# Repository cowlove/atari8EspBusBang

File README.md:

# Atari 8-bit ESP32 BusBang

```text
@@@@@@@@@@@@@@@@@@@@@@@@@@@@@@@@@@@@@@@@@@@@@@@@@@@@@@@@@@@@@@@@@@@@@@@@@@@@@@@
@     _   _             _  ___  _     _ _        _____ ____  ____ _________   @
@    / \ | |_ __ _ _ __(_)( _ )| |__ (_) |_     | ____/ ___||  _ \___ /___ \  @
@   / _ \| __/ _` | '__| |/ _ \| '_ \| | __|    |  _| \___ \| |_) ||_ \ __) | @
@  / ___ \ || (_| | |  | | (_) | |_) | | |_     | |___ ___) |  __/___) / __/  @
@ /_/   \_\__\__,_|_|  |_|\___/|_.__/|_|\__|    |_____|____/|_|  |____/_____| @
@                ____            ____                    _ _ _ _              @
@               | __ ) _   _ ___| __ )  __ _ _ __   __ _| | | | |             @
@               |  _ \| | | / __|  _ \ / _` | '_ \ / _` | | | | |             @
@               | |_) | |_| \__ \ |_) | (_| | | | | (_| |_|_|_|_|             @
@               |____/ \__,_|___/____/ \__,_|_| |_|\__, (_|_|_|_)             @
@                                                  |___/                      @
@@@@@@@@@@@@@@@@@@@@@@@@@@@@@@@@@@@@@@@@@@@@@@@@@@@@@@@@@@@@@@@@@@@@@@@@@@@@@@@
READY
█
```

## About the Project

Atari8EspBusBang uses a naked ESP32-S3 dev board to bit-bang the Atari 8-bit memory bus through the PBI port. The ESP32 has enough speed to handle the 6502's memory requests, overriding base memory and emulating extended memory, multi-bank cartridges, and SIO devices.  It implements a true software-defined PBI device.  The outside world, modern ideas, and high-level code all have direct access to the stock Atari system and memory at 960MB/sec.  

This started as a bus monitor for troubleshooting a flaky 800XL. Once it became clear that the ESP32 could also *respond* to bus requests, the project grew into a software-defined PBI device— and an ultimate extreme performance exercise on the ESP32. The bus-protocol loop runs bare-metal on the ESP32's second core; the first core handles utility tasks such as networking, PBI device logic, and flash disk-image access.

This idea pushes the ESP32 to its absolute performance limit, and the lower level parts of the project are intricate.  I'd like to eventually implement a simple module interface for adding functionality and trying ideas in easy code steps without needing to mess with or understand the low-level internals of this project.  

## Building the Hardware

The KiCad designs, parts list, PCB ordering notes, and assembly notes are in the [hardware README](hardware/README.md).  Total cost is about $20, and requires only through-hole soldering of headers. 

## Building the Firmware

The project depends on a specific pinned and lightly patched version of ESP-IDF v6.1, llvm-mos-sdk, and a few other tools.  Using the provided docker image is probably the easiest way to arrange for this. 

```
./tools/container/setup-build-env.sh container-runtime    # Install software needed to run podman  
./tools/container/container.sh pull                       # fetch/build docker image (6Gb/5min)
./tools/container/container.sh flash_spiffs /dev/ttyACM0  # first-time init of flash storage
./tools/container/container.sh flash /dev/ttyACM0         # build firmware and flash esp32 
```

Or you can install this all directly on your system and run esp-idf tools directly.  
```
./tools/container/setup-build-env.sh          # installs patched esp-idf,etc in ~/opt/ (6Gb/5min)
. ~/opt/atari8esp-idf-v6.1/export.sh          # set env to run esp-idf tools
./tools/flash_spiffs -p /dev/ttyACM0          # first-time init of flash storage 
idf.py --ccache flash -p /dev/ttyACM0         # build firmware and flash esp32
```

For the pinned Podman build environment, see [`tools/container/container.sh`](tools/container/container.sh) and [its README](tools/container/README.md).

## Contributing

Bug reports and focused contributions are welcome.  Please report issues with the environment setup scripts. 

## License

Distributed under GPL-2.0. See [LICENSE.txt](LICENSE.txt).

## Contact

Jim Evans — [jim@vheavy.com](mailto:jim@vheavy.com)

Project repository: <https://github.com/cowlove/atari8EspBusBang>

Project webpage: <http://cowlove.com/atari8EspBusBang/>

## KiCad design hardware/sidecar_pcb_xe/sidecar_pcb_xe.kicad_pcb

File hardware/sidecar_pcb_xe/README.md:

# sidecar_pcb_xe: the Sidecar carrier with bare modules, XE (speculative)

[sidecar_pcb_xl](../sidecar_pcb_xl/) for the 130XE: the same circuit, but
J1 is the XE's **cartridge + ECI card edge** (the footprint of the
[eci2Pbi adapter](../eci2Pbi/)) instead of the PBI connector. The board
plugs straight into the XE, with no adapter.

**Status: autorouted, not reviewed.** Routed by
[`tools/autoroute.sh`](../tools/autoroute.sh): DRC shows no clearance errors
and nothing unconnected, and the schematic and board agree. Not checked by a
human yet, and its fit in the XE's cartridge opening isn't verified (the body
is as wide as the two tabs, 80.6 mm, plus the 15.4 mm J8 wing on the right,
and stands 40 mm above them, plus the antennas).

## J1: ECI ↔ PBI

Each card-edge pin carries the XL board's net for the PBI pin the eci2Pbi
adapter wires it to:

| Card edge | Net (PBI pin) | Card edge | Net (PBI pin) |
|---|---|---|---|
| 5, 4, 3, 2 | A0–A3 (3–6) | 10, 9, 8, L | D0–D3 (21–24) |
| C, D, E, F | A4–A7 (7–9, 11) | 6, 7, 11, M | D4–D7 (25–28) |
| H, J, P, N, K | A8–A12 (12–16) | R | READ (46) |
| D1, E1, F1 | A13–A15 (17, 18, 20) | S | PHI2 (31) |
| ECI 1-1 | EXTSEL (2) | ECI B1 | IRQ (35) |
| ECI 1-2 | RESET (34) | **ECI C1 (HALT)** | **READY (36)** |
| ECI 1-4 | MPD (43) | ECI 1-5 | AUDIO (49) |
| ECI 1-6 | REFRESH (40) | 13, ECI 1-7 | VCC50_1 (47) |
| B, ECI H1 | GND | | |

- **HALT:** the adapter joins ECI C1 (HALT) to PBI 36 (READY), so this board
  does too: the halt line works on the XE as on the XL boards.
- **Unused:** the PBI's EXTDEC, CAS, RAS and NCs have no ECI pin; nothing else
  on the board uses them. The cartridge pins S4, S5, RD4, RD5, CCTL and ECI
  D1XX and RESERVED are left open, as on the adapter.
- **5 V:** both card-edge 5 V pins go to `VCC50_1`, which J6 joins to the
  board rail, as on the XL board (fit J6 to run from the Atari; remove it when
  powering from J4/J5).

## Layout

The tabs run along the bottom edge: the ECI tab on the left, the cartridge
tab on the right (J1 is the adapter's footprint turned 180°; either face of
the board can be the front, see the adapter for which way it goes in). The
modules' antennas and the microSD slot point off the top edge; the
regulators U3 and U4 are on the back. A wing past the cartridge tab, on the
right, carries the optional NTSC jack J8 (below U2's antenna keep-out) and
its ladder R18-R21, as on the XL board (see its README, "J8"). Board
96.1 × 60.1 mm with the tabs.
`sidecar_pcb_xe.kicad_dru` lets J1's fingers run to the board edge.

DRC leftovers, as on the XL board: U1/U2 differ from the library (their
thermal vias widened to 0.3 mm, see the XL README), the modules' silkscreen
overhangs the top edge, two GND pads reach the pour through a single thermal spoke, and the
Atari8 footprint library isn't in the library table (J1's footprint is
embedded in the board).

## Files

| File | |
|---|---|
| `sidecar_pcb_xe.kicad_sch` | Generated by [`../tools/make_sidecar_xe_schematic.py`](../tools/make_sidecar_xe_schematic.py) from the XL schematic: don't edit by hand |
| `sidecar_pcb_xe.kicad_pcb` | Built by [`../tools/make_sidecar_xe_pcb.py`](../tools/make_sidecar_xe_pcb.py) (XL footprints, adapter's J1, XE placement), then autorouted |
| `sidecar_pcb_xe.kicad_pro`, `.kicad_dru` | Project and the card-edge DRC rule |

To rebuild after an XL change (see [../AGENTS.md](../AGENTS.md)):

```
S=$(mktemp -d)
kicad-cli sch export netlist -o $S/xl.net hardware/sidecar_pcb_xl/sidecar_pcb_xl.kicad_sch
kicad-cli sch export netlist -o $S/eci.net hardware/eci2Pbi/atari8EciToPbi.kicad_sch
python3 hardware/tools/make_sidecar_xe_schematic.py hardware/sidecar_pcb_xl/sidecar_pcb_xl.kicad_sch $S/xl.net \
    hardware/eci2Pbi/atari8EciToPbi.kicad_sch $S/eci.net hardware/sidecar_pcb_xe/sidecar_pcb_xe.kicad_sch
kicad-cli sch export netlist -o $S/xe.net hardware/sidecar_pcb_xe/sidecar_pcb_xe.kicad_sch
/usr/bin/python3 hardware/tools/make_sidecar_xe_pcb.py hardware/sidecar_pcb_xl/sidecar_pcb_xl.kicad_pcb \
    hardware/eci2Pbi/atari8EciToPbi.kicad_pcb $S/xe.net hardware/sidecar_pcb_xe/sidecar_pcb_xe.kicad_pcb
hardware/tools/autoroute.sh hardware/sidecar_pcb_xe/sidecar_pcb_xe.kicad_pcb $S/xe-routed.kicad_pcb 60
cp $S/xe-routed.kicad_pcb hardware/sidecar_pcb_xe/sidecar_pcb_xe.kicad_pcb
```

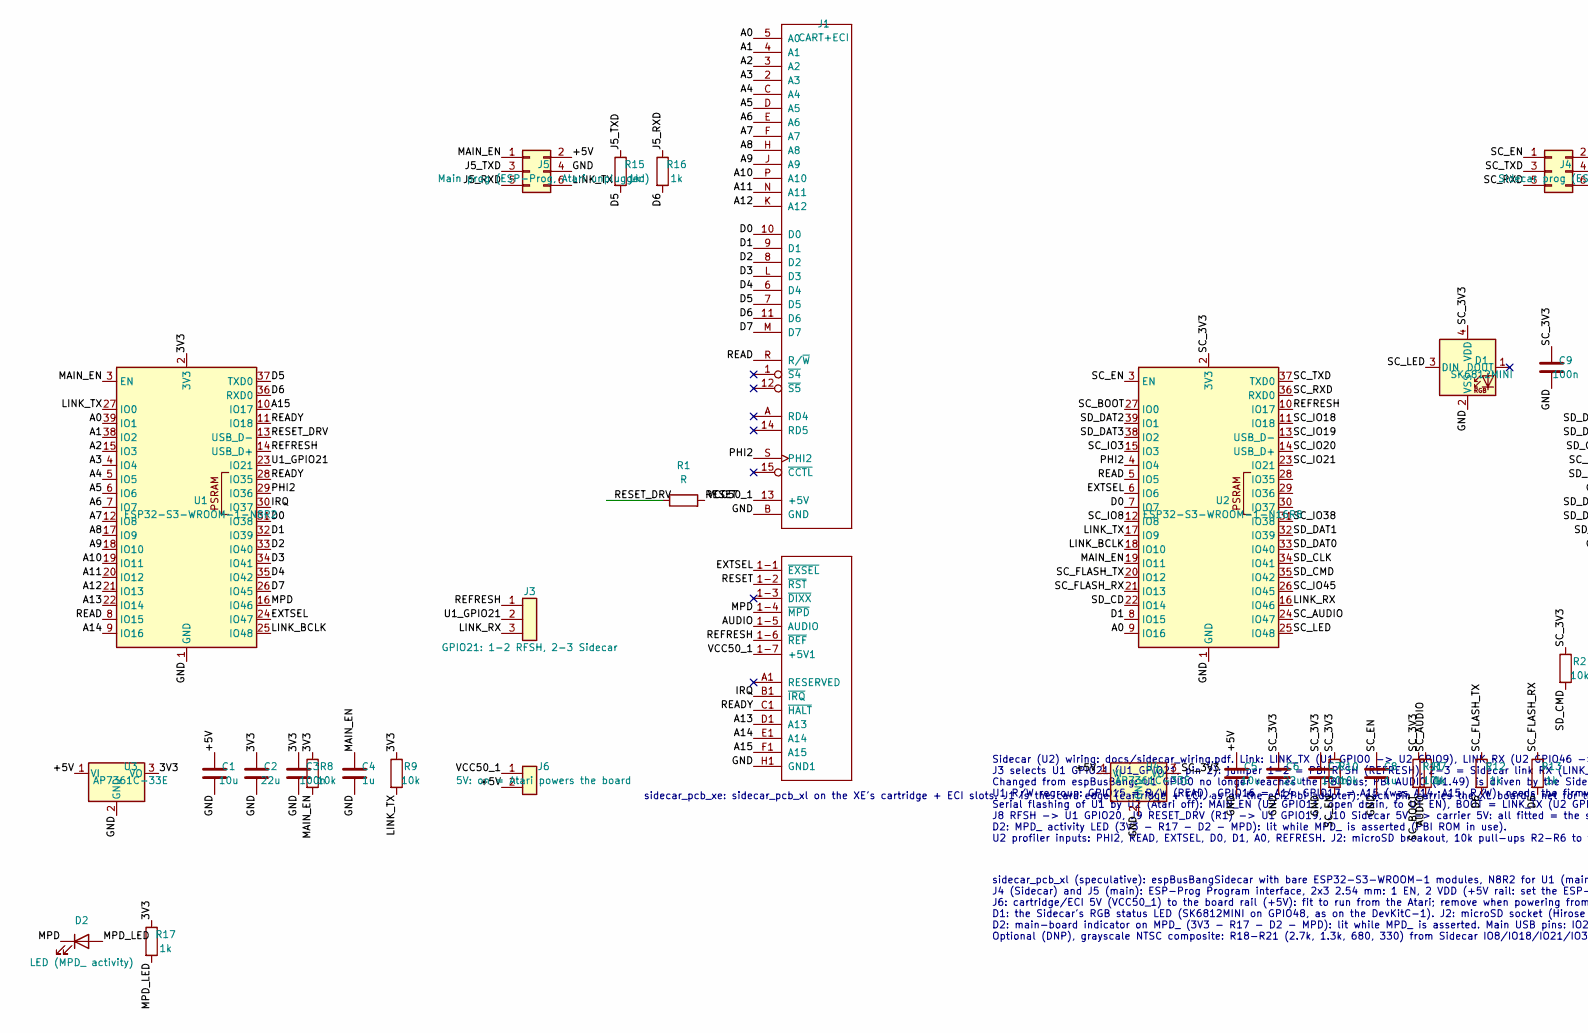
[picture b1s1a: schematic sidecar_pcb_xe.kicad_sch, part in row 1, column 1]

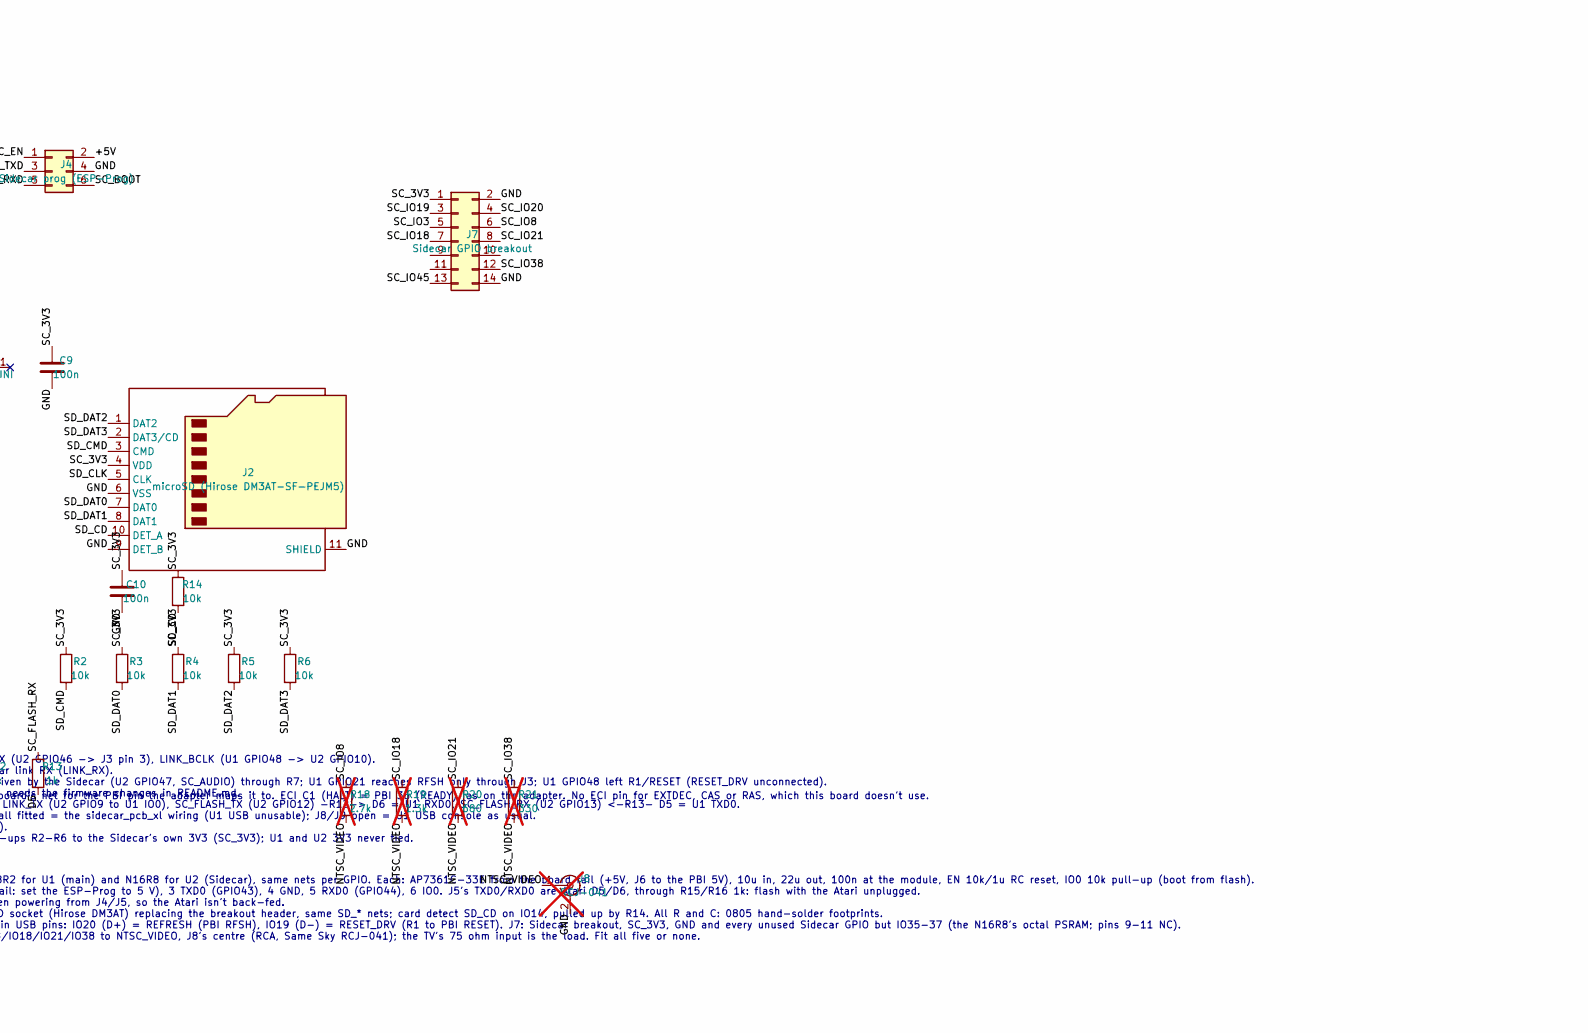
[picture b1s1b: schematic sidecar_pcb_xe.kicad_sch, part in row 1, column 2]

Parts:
C1, C5: 10u; C_0805_2012Metric_Pad1.18x1.45mm_HandSolder
C2, C6: 22u; C_0805_2012Metric_Pad1.18x1.45mm_HandSolder
C3, C7, C9, C10: 100n; C_0805_2012Metric_Pad1.18x1.45mm_HandSolder
C4, C8: 1u; C_0805_2012Metric_Pad1.18x1.45mm_HandSolder
D1: SK6812MINI; LED_SK6812MINI_PLCC4_3.5x3.5mm_P1.75mm
D2: LED (MPD_ activity); LED_0805_2012Metric_Pad1.15x1.40mm_HandSolder
J1: CART+ECI; CART+ECI_V3.0
J2: microSD (Hirose DM3AT-SF-PEJM5); microSD_HC_Hirose_DM3AT-SF-PEJM5
J3: GPIO21: 1-2 RFSH, 2-3 Sidecar; PinHeader_1x03_P2.54mm_Vertical
J4: Sidecar prog (ESP-Prog); PinHeader_2x03_P2.54mm_Vertical
J5: Main prog (ESP-Prog, Atari unplugged); PinHeader_2x03_P2.54mm_Vertical
J6: 5V: on = Atari powers the board; PinHeader_1x02_P2.54mm_Vertical
J7: Sidecar GPIO breakout; PinHeader_2x07_P2.54mm_Vertical
J8: RCJ-041; RCA_SameSky_RCJ-04x_Horizontal; not fitted
R1: R; R_0805_2012Metric_Pad1.20x1.40mm_HandSolder
R2, R3, R4, R5, R6, R8, R9, R10, R11, R14: 10k; R_0805_2012Metric_Pad1.20x1.40mm_HandSolder
R7, R12, R13, R15, R16, R17: 1k; R_0805_2012Metric_Pad1.20x1.40mm_HandSolder
R18: 2.7k; R_0805_2012Metric_Pad1.20x1.40mm_HandSolder; not fitted
R19: 1.3k; R_0805_2012Metric_Pad1.20x1.40mm_HandSolder; not fitted
R20: 680; R_0805_2012Metric_Pad1.20x1.40mm_HandSolder; not fitted
R21: 330; R_0805_2012Metric_Pad1.20x1.40mm_HandSolder; not fitted
U1: ESP32-S3-WROOM-1-N8R2; ESP32-S3-WROOM-1
U2: ESP32-S3-WROOM-1-N16R8; ESP32-S3-WROOM-1
U3, U4: AP7361C-33E; SOT-223-3_TabPin2

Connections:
/3V3: C2.1, C3.1, R8.1, R9.1, R17.1, U1.2 (3V3), U3.3 (VO)
/+5V: C1.1, C5.1, J4.2, J5.2, J6.2, U3.1 (VI), U4.1 (VI)
/A0: J1.5 (A0), U1.39 (IO1), U2.9 (IO16)
/A1: J1.4 (A1), U1.38 (IO2)
/A2: J1.3 (A2), U1.15 (IO3)
/A3: J1.2 (A3), U1.4 (IO4)
/A4: J1.C (A4), U1.5 (IO5)
/A5: J1.D (A5), U1.6 (IO6)
/A6: J1.E (A6), U1.7 (IO7)
/A7: J1.F (A7), U1.12 (IO8)
/A8: J1.H (A8), U1.17 (IO9)
/A9: J1.J (A9), U1.18 (IO10)
/A10: J1.P (A10), U1.19 (IO11)
/A11: J1.N (A11), U1.20 (IO12)
/A12: J1.K (A12), U1.21 (IO13)
/A13: J1.D1 (A13), U1.22 (IO14)
/A14: J1.E1 (A14), U1.9 (IO16)
/A15: J1.F1 (A15), U1.10 (IO17)
/AUDIO: J1.1-5 (AUDIO), R7.2
/D0: J1.10 (D0), U1.31 (IO38), U2.7 (IO7)
/D1: J1.9 (D1), U1.32 (IO39), U2.8 (IO15)
/D2: J1.8 (D2), U1.33 (IO40)
/D3: J1.L (D3), U1.34 (IO41)
/D4: J1.6 (D4), U1.35 (IO42)
/D5: J1.7 (D5), R13.2, R15.2, U1.37 (TXD0)
/D6: J1.11 (D6), R12.2, R16.2, U1.36 (RXD0)
/D7: J1.M (D7), U1.26 (IO45)
/EXTSEL: J1.1-1 (~EXSEL), U1.24 (IO47), U2.6 (IO6)
/GND: C1.2, C2.2, C3.2, C4.2, C5.2, C6.2, C7.2, C8.2, C9.2, C10.2, D1.2 (VSS), J1.B (GND), J1.H1 (GND1), J2.6 (VSS), J2.9 (DET_B), J2.11 (SHIELD), J4.4, J5.4, J7.2, J7.14, J8.2 (Ext), U1.1 (GND), U1.40 (GND), U1.41 (GND), U2.1 (GND), U2.40 (GND), U2.41 (GND), U3.2 (GND), U4.2 (GND)
/IRQ: J1.B1 (~IRQ), U1.30 (IO37)
/J5_RXD: J5.5, R16.1
/J5_TXD: J5.3, R15.1
/LINK_BCLK: U1.25 (IO48), U2.18 (IO10)
/LINK_RX: J3.3, U2.16 (IO46)
/LINK_TX: J5.6, R9.2, U1.27 (IO0), U2.17 (IO9)
/MAIN_EN: C4.1, J5.1, R8.2, U1.3 (EN), U2.19 (IO11)
/MPD: D2.1 (K), J1.1-4 (~MPD), U1.16 (IO46)
/MPD_LED: D2.2 (A), R17.2
/NTSC_VIDEO: J8.1 (In), R18.2, R19.2, R20.2, R21.2
/PHI2: J1.S (PHI2), U1.29 (IO36), U2.4 (IO4)
/READ: J1.R (R/~W), U1.8 (IO15), U2.5 (IO5)
/READY: J1.C1 (~HALT), U1.11 (IO18), U1.28 (IO35)
/REFRESH: J1.1-6 (~REF), J3.1, U1.14 (USB_D+), U2.10 (IO17)
/RESET: J1.1-2 (~RST), R1.2
/RESET_DRV: R1.1, U1.13 (USB_D-)
/SC_3V3: C6.1, C7.1, C9.1, C10.1, D1.4 (VDD), J2.4 (VDD), J7.1, R2.1, R3.1, R4.1, R5.1, R6.1, R10.1, R11.1, R14.1, U2.2 (3V3), U4.3 (VO)
/SC_AUDIO: R7.1, U2.24 (IO47)
/SC_BOOT: J4.6, R11.2, U2.27 (IO0)
/SC_EN: C8.1, J4.1, R10.2, U2.3 (EN)
/SC_FLASH_RX: R13.1, U2.21 (IO13)
/SC_FLASH_TX: R12.1, U2.20 (IO12)
/SC_IO3: J7.5, U2.15 (IO3)
/SC_IO8: J7.6, R18.1, U2.12 (IO8)
/SC_IO18: J7.7, R19.1, U2.11 (IO18)
/SC_IO19: J7.3, U2.13 (USB_D-)
/SC_IO20: J7.4, U2.14 (USB_D+)
/SC_IO21: J7.8, R20.1, U2.23 (IO21)
/SC_IO38: J7.12, R21.1, U2.31 (IO38)
/SC_IO45: J7.13, U2.26 (IO45)
/SC_LED: D1.3 (DIN), U2.25 (IO48)
/SC_RXD: J4.5, U2.36 (RXD0)
/SC_TXD: J4.3, U2.37 (TXD0)
/SD_CD: J2.10 (DET_A), R14.2, U2.22 (IO14)
/SD_CLK: J2.5 (CLK), U2.34 (IO41)
/SD_CMD: J2.3 (CMD), R2.2, U2.35 (IO42)
/SD_DAT0: J2.7 (DAT0), R3.2, U2.33 (IO40)
/SD_DAT1: J2.8 (DAT1), R4.2, U2.32 (IO39)
/SD_DAT2: J2.1 (DAT2), R5.2, U2.39 (IO1)
/SD_DAT3: J2.2 (DAT3/CD), R6.2, U2.38 (IO2)
/U1_GPIO21: J3.2, U1.23 (IO21)
/VCC50_1: J1.1-7 (+5V1), J1.13 (+5V), J6.1

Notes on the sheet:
Sidecar (U2) wiring: docs/sidecar_wiring.pdf. Link: LINK_TX (U1 GPIO0 -> U2 GPIO9), LINK_RX (U2 GPIO46 -> J3 pin 3), LINK_BCLK (U1 GPIO48 -> U2 GPIO10). J3 selects U1 GPIO21 (U1_GPIO21, pin 2): jumper 1-2 = PBI RFSH (REFRESH), 2-3 = Sidecar link RX (LINK_RX). Changed from espBusBang: U1 GPIO0 no lo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
sidecar_pcb_xl (speculative): espBusBangSidecar with bare ESP32-S3-WROOM-1 modules, N8R2 for U1 (main) and N16R8 for U2 (Sidecar), same nets per GPIO. Each: AP7361C-33E from the board rail (+5V, J6 to the PBI 5V), 10u in, 22u out, 100n at the module, EN 10k/1u RC reset, IO0 10k pull-up (boot from f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
sidecar_pcb_xe: sidecar_pcb_xl on the XE's cartridge + ECI slots. J1 is the card edge (cartridge + ECI, as on the eci2Pbi adapter); each pin carries the XL board's net for the PBI pin the adapter maps it to. ECI C1 (HALT) = PBI 36 (READY), as on the adapter. No ECI pin for EXTDEC, CAS or RAS, which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

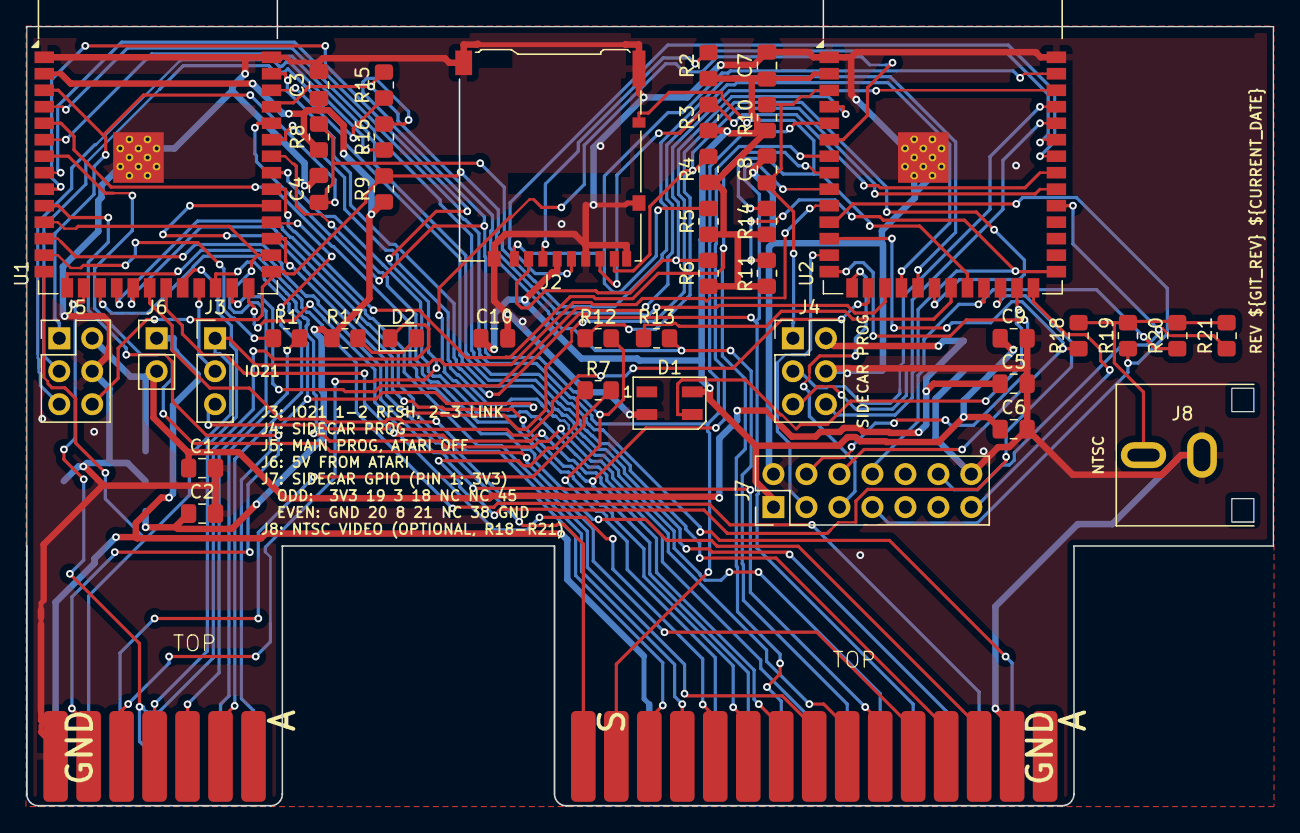
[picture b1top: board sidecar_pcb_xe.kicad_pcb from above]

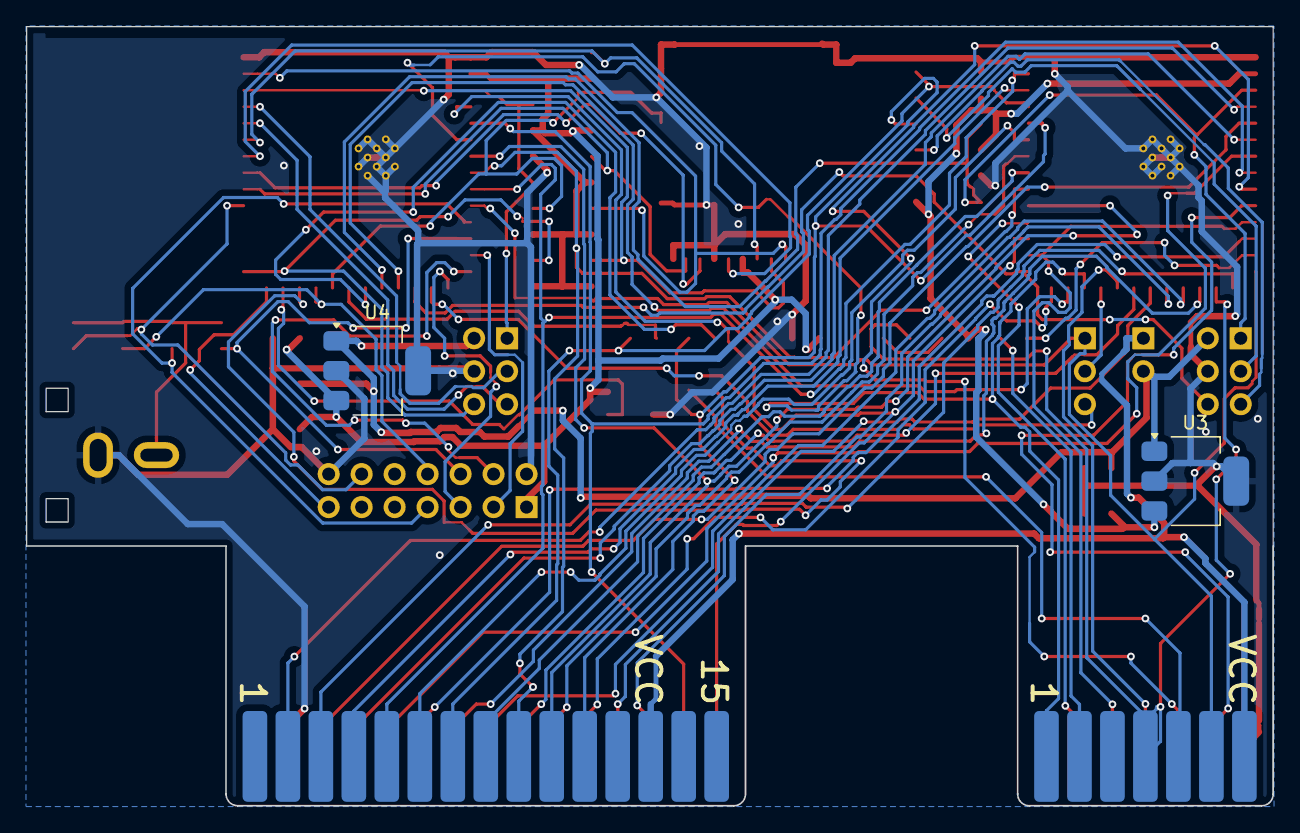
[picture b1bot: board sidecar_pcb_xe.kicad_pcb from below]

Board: 2 copper layers, 96.0 x 60.0 mm, 45 parts (2 on the bottom side), 71 nets.

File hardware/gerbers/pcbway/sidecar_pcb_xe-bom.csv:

Item #,Designator,Qty,Manufacturer,Mfg Part #,Description / Value,Package/Footprint,Type,Your Instructions / Notes
1,"C1,C5",2,Samsung,CL21A106KAYNNNE,10uF 25V X5R MLCC,0805,SMD,
2,"C2,C6",2,Samsung,CL21A226MAQNNNE,22uF 25V X5R MLCC,0805,SMD,
3,"C3,C7,C9,C10",4,Samsung,CL21B104KBCNNNC,100nF 50V X7R MLCC,0805,SMD,
4,"C4,C8",2,Samsung,CL21B105KBFNNNE,1uF 50V X7R MLCC,0805,SMD,
5,D1,1,OPSCO,SK6812MINI,"RGB LED, integrated driver",PLCC4 3.5x3.5mm,SMD,
6,D2,1,Hubei KENTO,KT-0805G,Green LED,0805,SMD,"Any 0805 LED, colour free"
7,J2,1,Hirose,DM3AT-SF-PEJM5,"microSD socket, push-push",SMD,SMD,
8,J3,1,Generic,1x03 2.54mm male header,"3-pin 2.54mm male pin header, vertical",THT,THT,
9,"J4,J5",2,Generic,2x03 2.54mm male header,"6-pin 2.54mm male pin header, vertical",THT,THT,
10,J6,1,Generic,1x02 2.54mm male header,"2-pin 2.54mm male pin header, vertical",THT,THT,
11,J7,1,Generic,2x07 2.54mm male header,"14-pin 2.54mm male pin header, vertical",THT,THT,
12,R1,1,UNI-ROYAL,0805W8F0000T5E,0 ohm resistor,0805,SMD,
13,"R2,R3,R4,R5,R6,R8,R9,R10,R11,R14",10,UNI-ROYAL,0805W8F1002T5E,10k 1% resistor,0805,SMD,
14,"R7,R12,R13,R15,R16,R17",6,UNI-ROYAL,0805W8F1001T5E,1k 1% resistor,0805,SMD,
15,U1,1,Espressif,ESP32-S3-WROOM-1-N8R2,"ESP32-S3 module, 8MB flash, 2MB PSRAM",SMD module,SMD,
16,U2,1,Espressif,ESP32-S3-WROOM-1-N16R8,"ESP32-S3 module, 16MB flash, 8MB octal PSRAM",SMD module,SMD,
17,"U3,U4",2,Diodes Inc,AP7361C-33E-13,3.3V 1A LDO regulator,SOT-223,SMD,Mounted on the bottom side

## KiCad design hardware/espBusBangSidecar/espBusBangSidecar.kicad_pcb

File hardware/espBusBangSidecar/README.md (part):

# espBusBangSidecar: the carrier with a Sidecar

A next-generation version of the [espBusBang](../espBusBang/) carrier with a
second ESP32-S3-DevKitC-1, the **Sidecar**, beside the main board. The
Sidecar talks to the main board over the I2S link and can run disk I/O, a bus
profiler, a microSD card and an audio output.

**Status: autorouted, not reviewed.** Placed by
[`../tools/place_sidecar_devkitc.py`](../tools/place_sidecar_devkitc.py) and
routed by [`../tools/autoroute.sh`](../tools/autoroute.sh) (see
[../AGENTS.md](../AGENTS.md)): no clearance errors, nothing unconnected,
schematic parity clean. Not checked by a human or ordered yet.

**Mounting, as on espBusBang:** J1 (PBI) is soldered in from the **back**,
the DevKitC sockets on the front, so the DevKitCs face out from the Atari:
there is no room for them on J1's side. (Both footprints sit on the front
layer in KiCad, as on espBusBang: don't flip J1.) U1 and J1 are exactly where
espBusBang has them; U2 sits beside U1, on the side away from J1's mounting
edge, and the headers (J2–J5, J7–J10) and the MPD_ LED (D2) run in a strip
beyond U2, outside the sockets. The small SMD resistors sit between the
DevKitCs' header rows, as R1 does on espBusBang: solder them before the
sockets. Board 71.3 × 63.8 mm; the right edge moved out 0.26 mm so U1's
outer pads clear the 0.5 mm edge clearance (espBusBang has 0.38 mm).

DRC leftovers: J1's pins 49/50 sit 0.38 mm from the top edge (as on
espBusBang); the DevKitC courtyards overlap the parts under them and J1
(intended); silkscreen overlaps from the DevKitC footprint's pin labels.

**The main board's firmware must change before this board can be used**: see
[Software changes required](#software-changes-required). The R/W pin moved.

## Files

| File | |
|---|---|
| `espBusBangSidecar.kicad_sch` | Generated: don't edit by hand |
| `espBusBangSidecar.kicad_pro`, `.kicad_pcb` | Board: from espBusBang's, updated by [`../tools/netlist_to_pcb.py`](../tools/netlist_to_pcb.py), placed and routed as above |
| [`../tools/make_sidecar_schematic.py`](../tools/make_sidecar_schematic.py) | Builds the schematic from `../espBusBang/atariEspBusBang3.kicad_sch` |
| [`../../docs/sidecar_wiring.pdf`](../../docs/sidecar_wiring.pdf) | The board-to-board wiring as a drawing (from [`../tools/sidecar_wiring.py`](../tools/sidecar_wiring.py)) |

To change the schematic, edit the script and regenerate:

```
python3 hardware/tools/make_sidecar_schematic.py \
    hardware/espBusBang/atariEspBusBang3.kicad_sch \
    hardware/espBusBangSidecar/espBusBangSidecar.kicad_sch
kicad-cli sch erc --severity-all -o erc.rpt hardware/espBusBangSidecar/espBusBangSidecar.kicad_sch
kicad-cli sch export netlist -o sidecar.net hardware/espBusBangSidecar/espBusBangSidecar.kicad_sch
```

ERC reports 83 items. None are new kinds of problem: the same classes the
original board has (labels on one-pin nets, no
PWR_FLAG, J1 pins of type "Unspecified"), plus "library not in the
configuration" when KiCad's library tables lack Espressif and the TE
connector.

## Parts added

Every resistor and LED, R1 from espBusBang included, uses KiCad's 0805
hand-solder footprints (longer pads, for an iron); only headers and
connectors are through-hole.

| Ref | Part | Footprint |
|---|---|---|
| U2 | ESP32-S3-DevKitC-1 (the Sidecar) | `Espressif:ESP32-S2-DevKitC-1`, as U1 |
| J2 | 1×8 header for a microSD breakout, in the card's pin order: DAT2, DAT3, CMD, 3V3, CLK, GND, DAT0, DAT1. An SDIO breakout (pins D0–D3, CMD, CLK) wires 1:1 and runs 4-bit. An SPI-only breakout works too, at about a quarter of the speed: CS → 2, DI/MOSI → 3, CLK → 5, DO/MISO → 7, GND → 6; if it has its own regulator, feed it 5 V (`SC_5V`) rather than pin 4's 3.3 V. The Sidecar tries SD mode, then SPI mode | `PinHeader_1x08_P2.54mm_Vertical` |
| R2–R6 | 10 k pull-ups to the Sidecar's 3V3 on SD CMD and DAT0–DAT3 | `R_0805_2012Metric_Pad1.20x1.40mm_HandSolder` |
| R7 | 1 k series resistor, Sidecar audio to the PBI audio input; sets the level, a starting guess | 0805 hand-solder |
| R12, R13 | 1 k series resistors in the Sidecar's flashing UART, to the main board's UART0 (Atari D6/D5) | 0805 hand-solder |
| J3 | 1×3 header: main GPIO21 selector | `PinHeader_1x03_P2.54mm_Vertical` |
| J8, J9, J10 | 2-pin jumpers: RFSH and RESET to the main USB pins, Sidecar 5V to the carrier's 5V | `PinHeader_1x02_P2.54mm_Vertical` |
| J4 | Sidecar ESP-Prog header (2×3): 1 EN (`SC_EN`), 2 VDD (`SC_5V`), 3 TXD0 (GPIO43), 4 GND, 5 RXD0 (GPIO44), 6 IO0 (`SC_BOOT`), as on sidecar_pcb_xl. The DevKitC's own USB-UART is on the same TXD0/RXD0: use one or the other | `PinHeader_2x03_P2.54mm_Vertical` |
| J5, R15, R16 | Main ESP-Prog header: 1 EN (`MAIN_EN`), 2 VDD (`VCC50_1`), 3/5 TXD0/RXD0 through R15/R16 (1 k) to Atari D5/D6, 6 IO0 (`LINK_TX`). **Atari unplugged** (its UART is the data bus); an ESP-Prog at 5 V back-feeds the PBI 5 V, as the DevKitC's USB does | 2×3 header, 0805 R |
| J7 | Sidecar GPIO breakout (2×8): 1 `SC_3V3`, 2 GND, 3–15 the unused Sidecar GPIOs (19, 20, 3, 8, 14, 18, 21, 35, 36, 37, 38, 45, 48), 16 GND. On the DevKitC, GPIO19/20 are its USB port and GPIO48 its RGB LED; GPIO3 and 45 are straps | `PinHeader_2x08_P2.54mm_Vertical` |
| D2, R17 | MPD_ activity LED: main 3V3 → R17 (1 k) → D2 → `MPD`, lit while MPD_ is asserted | `LED_0805_2012Metric_Pad1.15x1.40mm_HandSolder`, 0805 R |

## J3: main board GPIO21

| Jumper | Main GPIO21 is | Use with |
|---|---|---|
| 1–2 | the PBI RFSH line (`refresh_`), as on espBusBang | firmware built without the Sidecar (`CONFIG_A8BB_SIDECAR_ENABLE` off), Sidecar unused or running stand-alone |
| 2–3 | the link's RX, from Sidecar GPIO46 | firmware built with `CONFIG_A8BB_SIDECAR_ENABLE` |

The Sidecar's own RFSH input (GPIO17) is wired to RFSH directly, whichever
way J3 is set.

## J8–J10: standing in for sidecar_pcb_xl

Three 2-pin jumpers let this board run the [sidecar_pcb_xl](../sidecar_pcb_xl/)
wiring, where the bare main module has no USB port and its USB pins carry
two Atari signals:

| Jumper | Joins | Fitted |
|---|---|---|
| J8 | PBI RFSH (`REFRESH`) and main GPIO20, USB D+ (`U1_GPIO20`) | `refresh_` on its own pin, in every build |
| J9 | R1's ESP end (`RESET_DRV`, R1 to PBI RESET) and main GPIO19, USB D− (`U1_GPIO19`) | the Atari's reset under the main board's control |
| J10 | the carrier's 5 V (`VCC50_1`: PBI 5 V, the main DevKitC's 5V pin) and the Sidecar's 5V pin (`SC_5V`) | one 5 V for both boards |

- **J8 and J9 open** (the default): the main DevKitC's USB port works as it
  does today, and it's the console.
- **J8 and J9 fitted**: the main board's USB lines carry RFSH and RESET, so
  its USB port is unusable (don't plug it in); its console is the link.
  Firmware must be built for the sidecar_pcb_xl pin layout (below).
- **J10 open**: the Sidecar runs from its own USB, and nothing it's plugged
  into reaches the Atari's 5 V. **Fitted**: the Atari powers it too.

With J3 on 2–3 and J8–J10 fitted, this board is wired as sidecar_pcb_xl, except
for the DevKitC's own extras (its USB-serial bridge on main D5/D6, its LED).

## D2: MPD_ activity LED

The same indicator as sidecar_pcb_xl's (its README has the details): D2 lights
whenever MPD_ is asserted, which core 1 does while the 6502 runs the PBI ROM,
so it flickers with PBI requests. The main board only ever pulls MPD_ low, so
the LED can't cause a drive conflict. Fault blinking (only with the bus cold)
can be developed here for the bare-module board.

## Net changes on the main board (U1) vs espBusBang

| U1 pin | espBusBang | This board | Why |
|---|---|---|---|
| GPIO0 | `AUDIO` (PBI 49) | `LINK_TX` → Sidecar GPIO9 | The link's TX loaded PBI audio and could keep the link from locking (miner6 board 5). PBI audio is now driven by the Sidecar. |
| GPIO21 | `REFRESH` (PBI RFSH) | J3 pin 2 | Shared between `refresh_` and the link's RX; J3 picks. |
| GPIO48 | R1 → `RESET` | `LINK_BCLK` → Sidecar GPIO10 | BCLK would toggle the Atari's reset through R1. R1's ESP end (`RESET_DRV`) moves to J9. |
| GPIO19 (USB D−) | USB port only | also J9 → `RESET_DRV` → R1 → `RESET` | the sidecar_pcb_xl layout, jumper-selectable |
| GPIO20 (USB D+) | USB port only | also J8 → `REFRESH` | the sidecar_pcb_xl layout, jumper-selectable |
| GPIO15 | `A14` | `READ` (R/W) | **R/W regroup** (below) |
| GPIO16 | `A15` | `A14` | R/W regroup |
| GPIO17 | `READ` (R/W) | `A15` | R/W regroup |

### The R/W regroup

`r0` (GPIO_IN_REG) used to carry A0–A15 contiguously at bits 1–16 and R/W at
bit 17. Core 1's ctrl[] index is the 6 page bits A8–A13 with R/W as bit 6,
so it took an `srli`/`and`/`or` to splice R/W in. With R/W at bit 15, right
above A13, one `extui r0, 9, 7` gives the index:

```
today                                  regrouped
extui  a4, r0, 15, 2   ; block         extui  a4, r0, 16, 2   ; block
srli   a10, r0, 11     ; R/W           addx4  a4, a4, base
addx4  a4, a4, base                    l32i   a4, a4, 4
extui  a3, r0, 9, 6    ; page          extui  a3, r0, 9, 7    ; page + R/W
l32i   a4, a4, 4                       addx2  a3, a3, a4
and    a10, a10, 64                    l16ui  a3, a3, 0
or     a10, a3, a10                    ee.wr_mask_gpio_out a3, a3
addx2  a3, a10, a4
l16ui  a3, a3, 0
ee.wr_mask_gpio_out a3, a3
```

Three cycles (~12.5 ns) off the address-read-to-extSel_ path (P1 to P2: 15 to
12 static cycles) and off every loop. The cost: the address is no longer a
contiguous bit field in `r0`.

## The Sidecar (U2)

| U2 pin | Net | Use |
|---|---|---|
| GPIO9 | `LINK_TX` | link RX, from main GPIO0 |
| GPIO46 | `LINK_RX` | link TX, to main GPIO21 via J3 2–3 |
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
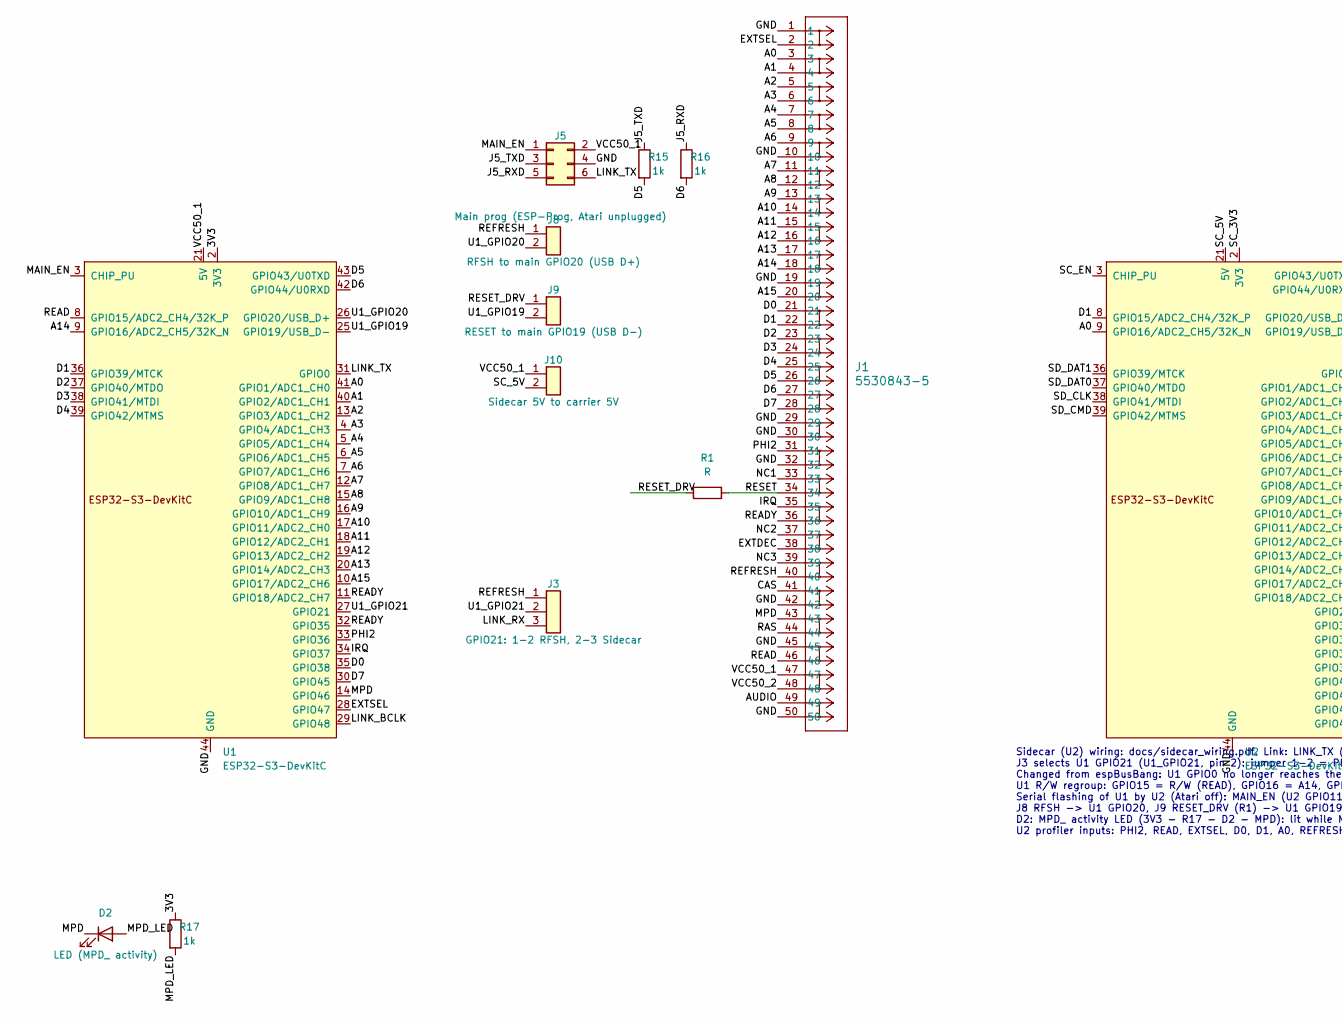
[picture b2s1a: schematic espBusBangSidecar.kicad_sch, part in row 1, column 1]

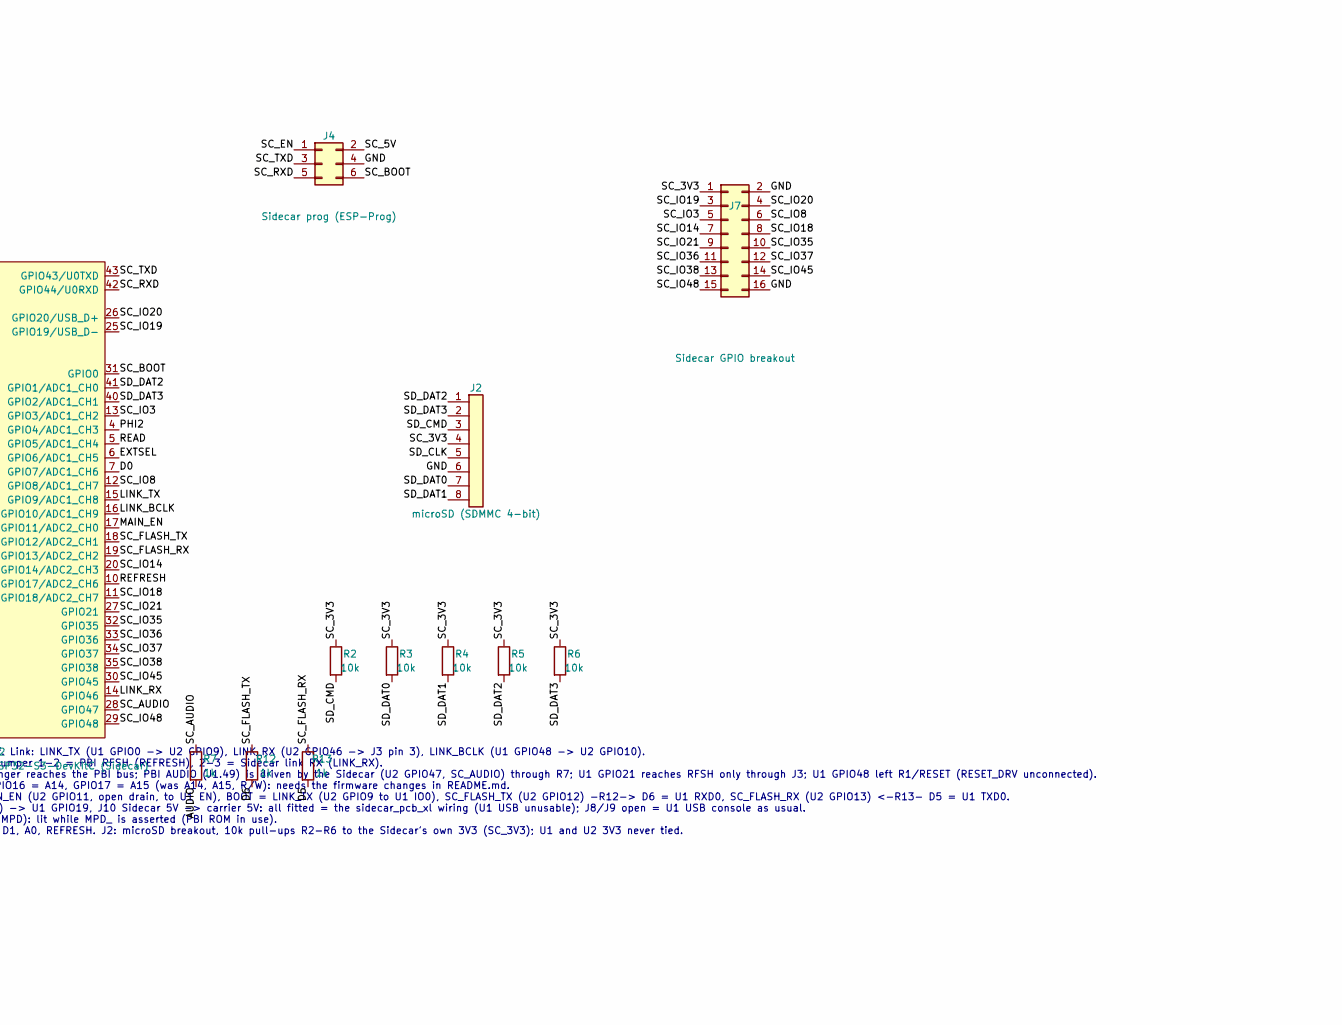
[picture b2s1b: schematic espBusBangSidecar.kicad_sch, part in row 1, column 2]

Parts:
D2: LED (MPD_ activity); LED_0805_2012Metric_Pad1.15x1.40mm_HandSolder
J1: 5530843-5; CONN50_5530843-5_TEC
J2: microSD (SDMMC 4-bit); PinHeader_1x08_P2.54mm_Vertical
J3: GPIO21: 1-2 RFSH, 2-3 Sidecar; PinHeader_1x03_P2.54mm_Vertical
J4: Sidecar prog (ESP-Prog); PinHeader_2x03_P2.54mm_Vertical
J5: Main prog (ESP-Prog, Atari unplugged); PinHeader_2x03_P2.54mm_Vertical
J7: Sidecar GPIO breakout; PinHeader_2x08_P2.54mm_Vertical
J8: RFSH to main GPIO20 (USB D+); PinHeader_1x02_P2.54mm_Vertical
J9: RESET to main GPIO19 (USB D-); PinHeader_1x02_P2.54mm_Vertical
J10: Sidecar 5V to carrier 5V; PinHeader_1x02_P2.54mm_Vertical
R1: R; R_0805_2012Metric_Pad1.20x1.40mm_HandSolder
R2, R3, R4, R5, R6: 10k; R_0805_2012Metric_Pad1.20x1.40mm_HandSolder
R7, R12, R13, R15, R16, R17: 1k; R_0805_2012Metric_Pad1.20x1.40mm_HandSolder
U1: ESP32-S3-DevKitC; ESP32-S2-DevKitC-1
U2: ESP32-S3-DevKitC (Sidecar); ESP32-S2-DevKitC-1

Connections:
/3V3: R17.1, U1.1 (3V3), U1.2 (3V3)
/A0: J1.3, U1.41 (GPIO1/ADC1_CH0), U2.9 (GPIO16/ADC2_CH5/32K_N)
/A1: J1.4, U1.40 (GPIO2/ADC1_CH1)
/A2: J1.5, U1.13 (GPIO3/ADC1_CH2)
/A3: J1.6, U1.4 (GPIO4/ADC1_CH3)
/A4: J1.7, U1.5 (GPIO5/ADC1_CH4)
/A5: J1.8, U1.6 (GPIO6/ADC1_CH5)
/A6: J1.9, U1.7 (GPIO7/ADC1_CH6)
/A7: J1.11, U1.12 (GPIO8/ADC1_CH7)
/A8: J1.12, U1.15 (GPIO9/ADC1_CH8)
/A9: J1.13, U1.16 (GPIO10/ADC1_CH9)
/A10: J1.14, U1.17 (GPIO11/ADC2_CH0)
/A11: J1.15, U1.18 (GPIO12/ADC2_CH1)
/A12: J1.16, U1.19 (GPIO13/ADC2_CH2)
/A13: J1.17, U1.20 (GPIO14/ADC2_CH3)
/A14: J1.18, U1.9 (GPIO16/ADC2_CH5/32K_N)
/A15: J1.20, U1.10 (GPIO17/ADC2_CH6)
/AUDIO: J1.49, R7.2
/CAS: J1.41
/D0: J1.21, U1.35 (GPIO38), U2.7 (GPIO7/ADC1_CH6)
/D1: J1.22, U1.36 (GPIO39/MTCK), U2.8 (GPIO15/ADC2_CH4/32K_P)
/D2: J1.23, U1.37 (GPIO40/MTDO)
/D3: J1.24, U1.38 (GPIO41/MTDI)
/D4: J1.25, U1.39 (GPIO42/MTMS)
/D5: J1.26, R13.2, R15.2, U1.43 (GPIO43/U0TXD)
/D6: J1.27, R12.2, R16.2, U1.42 (GPIO44/U0RXD)
/D7: J1.28, U1.30 (GPIO45)
/EXTDEC: J1.38
/EXTSEL: J1.2, U1.28 (GPIO47), U2.6 (GPIO6/ADC1_CH5)
/GND: J1.1, J1.10, J1.19, J1.29, J1.30, J1.32, J1.42, J1.45, J1.50, J2.6, J4.4, J5.4, J7.2, J7.16, U1.22 (GND), U1.23 (GND), U1.24 (GND), U1.44 (GND), U2.22 (GND), U2.23 (GND), U2.24 (GND), U2.44 (GND)
/IRQ: J1.35, U1.34 (GPIO37)
/J5_RXD: J5.5, R16.1
/J5_TXD: J5.3, R15.1
/LINK_BCLK: U1.29 (GPIO48), U2.16 (GPIO10/ADC1_CH9)
/LINK_RX: J3.3, U2.14 (GPIO46)
/LINK_TX: J5.6, U1.31 (GPIO0), U2.15 (GPIO9/ADC1_CH8)
/MAIN_EN: J5.1, U1.3 (CHIP_PU), U2.17 (GPIO11/ADC2_CH0)
/MPD: D2.1 (K), J1.43, U1.14 (GPIO46)
/MPD_LED: D2.2 (A), R17.2
/NC1: J1.33
/NC2: J1.37
/NC3: J1.39
/PHI2: J1.31, U1.33 (GPIO36), U2.4 (GPIO4/ADC1_CH3)
/RAS: J1.44
/READ: J1.46, U1.8 (GPIO15/ADC2_CH4/32K_P), U2.5 (GPIO5/ADC1_CH4)
/READY: J1.36, U1.11 (GPIO18/ADC2_CH7), U1.32 (GPIO35)
/REFRESH: J1.40, J3.1, J8.1, U2.10 (GPIO17/ADC2_CH6)
/RESET: J1.34, R1.2
/RESET_DRV: J9.1, R1.1
/SC_3V3: J2.4, J7.1, R2.1, R3.1, R4.1, R5.1, R6.1, U2.1 (3V3), U2.2 (3V3)
/SC_5V: J4.2, J10.2, U2.21 (5V)
/SC_AUDIO: R7.1, U2.28 (GPIO47)
/SC_BOOT: J4.6, U2.31 (GPIO0)
/SC_EN: J4.1, U2.3 (CHIP_PU)
/SC_FLASH_RX: R13.1, U2.19 (GPIO13/ADC2_CH2)
/SC_FLASH_TX: R12.1, U2.18 (GPIO12/ADC2_CH1)
/SC_IO3: J7.5, U2.13 (GPIO3/ADC1_CH2)
/SC_IO8: J7.6, U2.12 (GPIO8/ADC1_CH7)
/SC_IO14: J7.7, U2.20 (GPIO14/ADC2_CH3)
/SC_IO18: J7.8, U2.11 (GPIO18/ADC2_CH7)
/SC_IO19: J7.3, U2.25 (GPIO19/USB_D-)
/SC_IO20: J7.4, U2.26 (GPIO20/USB_D+)
/SC_IO21: J7.9, U2.27 (GPIO21)
/SC_IO35: J7.10, U2.32 (GPIO35)
/SC_IO36: J7.11, U2.33 (GPIO36)
/SC_IO37: J7.12, U2.34 (GPIO37)
/SC_IO38: J7.13, U2.35 (GPIO38)
/SC_IO45: J7.14, U2.30 (GPIO45)
/SC_IO48: J7.15, U2.29 (GPIO48)
/SC_RXD: J4.5, U2.42 (GPIO44/U0RXD)
/SC_TXD: J4.3, U2.43 (GPIO43/U0TXD)
/SD_CLK: J2.5, U2.38 (GPIO41/MTDI)
/SD_CMD: J2.3, R2.2, U2.39 (GPIO42/MTMS)
/SD_DAT0: J2.7, R3.2, U2.37 (GPIO40/MTDO)
/SD_DAT1: J2.8, R4.2, U2.36 (GPIO39/MTCK)
/SD_DAT2: J2.1, R5.2, U2.41 (GPIO1/ADC1_CH0)
/SD_DAT3: J2.2, R6.2, U2.40 (GPIO2/ADC1_CH1)
/U1_GPIO19: J9.2, U1.25 (GPIO19/USB_D-)
/U1_GPIO20: J8.2, U1.26 (GPIO20/USB_D+)
/U1_GPIO21: J3.2, U1.27 (GPIO21)
/VCC50_1: J1.47, J5.2, J10.1, U1.21 (5V)
/VCC50_2: J1.48

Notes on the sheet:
Sidecar (U2) wiring: docs/sidecar_wiring.pdf. Link: LINK_TX (U1 GPIO0 -> U2 GPIO9), LINK_RX (U2 GPIO46 -> J3 pin 3), LINK_BCLK (U1 GPIO48 -> U2 GPIO10). J3 selects U1 GPIO21 (U1_GPIO21, pin 2): jumper 1-2 = PBI RFSH (REFRESH), 2-3 = Sidecar link RX (LINK_RX). Changed from espBusBang: U1 GPIO0 no lo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

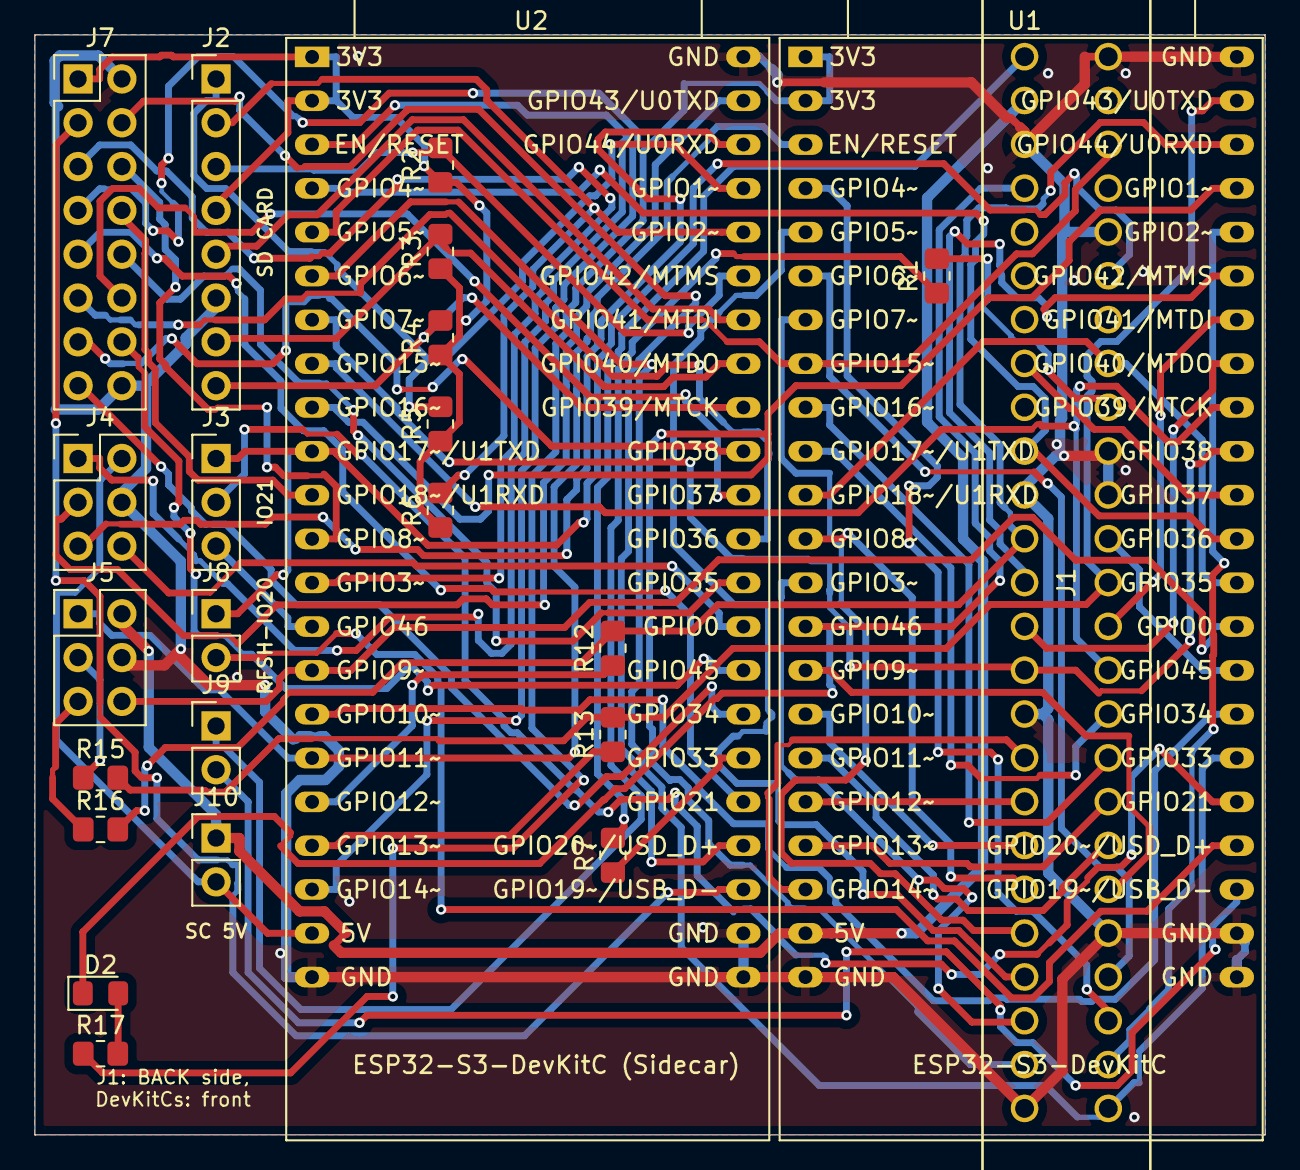
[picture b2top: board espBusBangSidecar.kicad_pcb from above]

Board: 2 copper layers, 71.3 x 63.8 mm, 24 parts (0 on the bottom side), 75 nets.

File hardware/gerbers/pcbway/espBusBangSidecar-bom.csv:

Item #,Designator,Qty,Manufacturer,Mfg Part #,Description / Value,Package/Footprint,Type,Your Instructions / Notes
1,D2,1,Hubei KENTO,KT-0805G,Green LED,0805,SMD,"Any 0805 LED, colour free"
2,J1,1,TE Connectivity,5530843-5,50-pos 2.54mm card edge connector (PBI),THT,THT,"Insert from the BOTTOM side (opposite the modules), solder on top. The footprint and its silkscreen are on the top layer"
3,J2,1,Generic,1x08 2.54mm male header,"8-pin 2.54mm male pin header, vertical",THT,THT,
4,J3,1,Generic,1x03 2.54mm male header,"3-pin 2.54mm male pin header, vertical",THT,THT,
5,"J4,J5",2,Generic,2x03 2.54mm male header,"6-pin 2.54mm male pin header, vertical",THT,THT,
6,J7,1,Generic,2x08 2.54mm male header,"16-pin 2.54mm male pin header, vertical",THT,THT,
7,"J8,J9,J10",3,Generic,1x02 2.54mm male header,"2-pin 2.54mm male pin header, vertical",THT,THT,
8,R1,1,UNI-ROYAL,0805W8F0000T5E,0 ohm resistor,0805,SMD,
9,"R2,R3,R4,R5,R6",5,UNI-ROYAL,0805W8F1002T5E,10k 1% resistor,0805,SMD,
10,"R7,R12,R13,R15,R16,R17",6,UNI-ROYAL,0805W8F1001T5E,1k 1% resistor,0805,SMD,
11,"U1,U2",2,Generic,1x22 2.54mm female header,Socket for an ESP32-S3-DevKitC-1: two 1x22 2.54mm female headers per designator,THT,THT,Fit 2 x 1x22 female headers per designator (4 total for U1+U2); DevKitC boards NOT supplied
